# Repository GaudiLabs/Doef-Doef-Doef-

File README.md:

# Doef-Doef-Doef-
Groove Box Synthesiszer with SMD Sliders

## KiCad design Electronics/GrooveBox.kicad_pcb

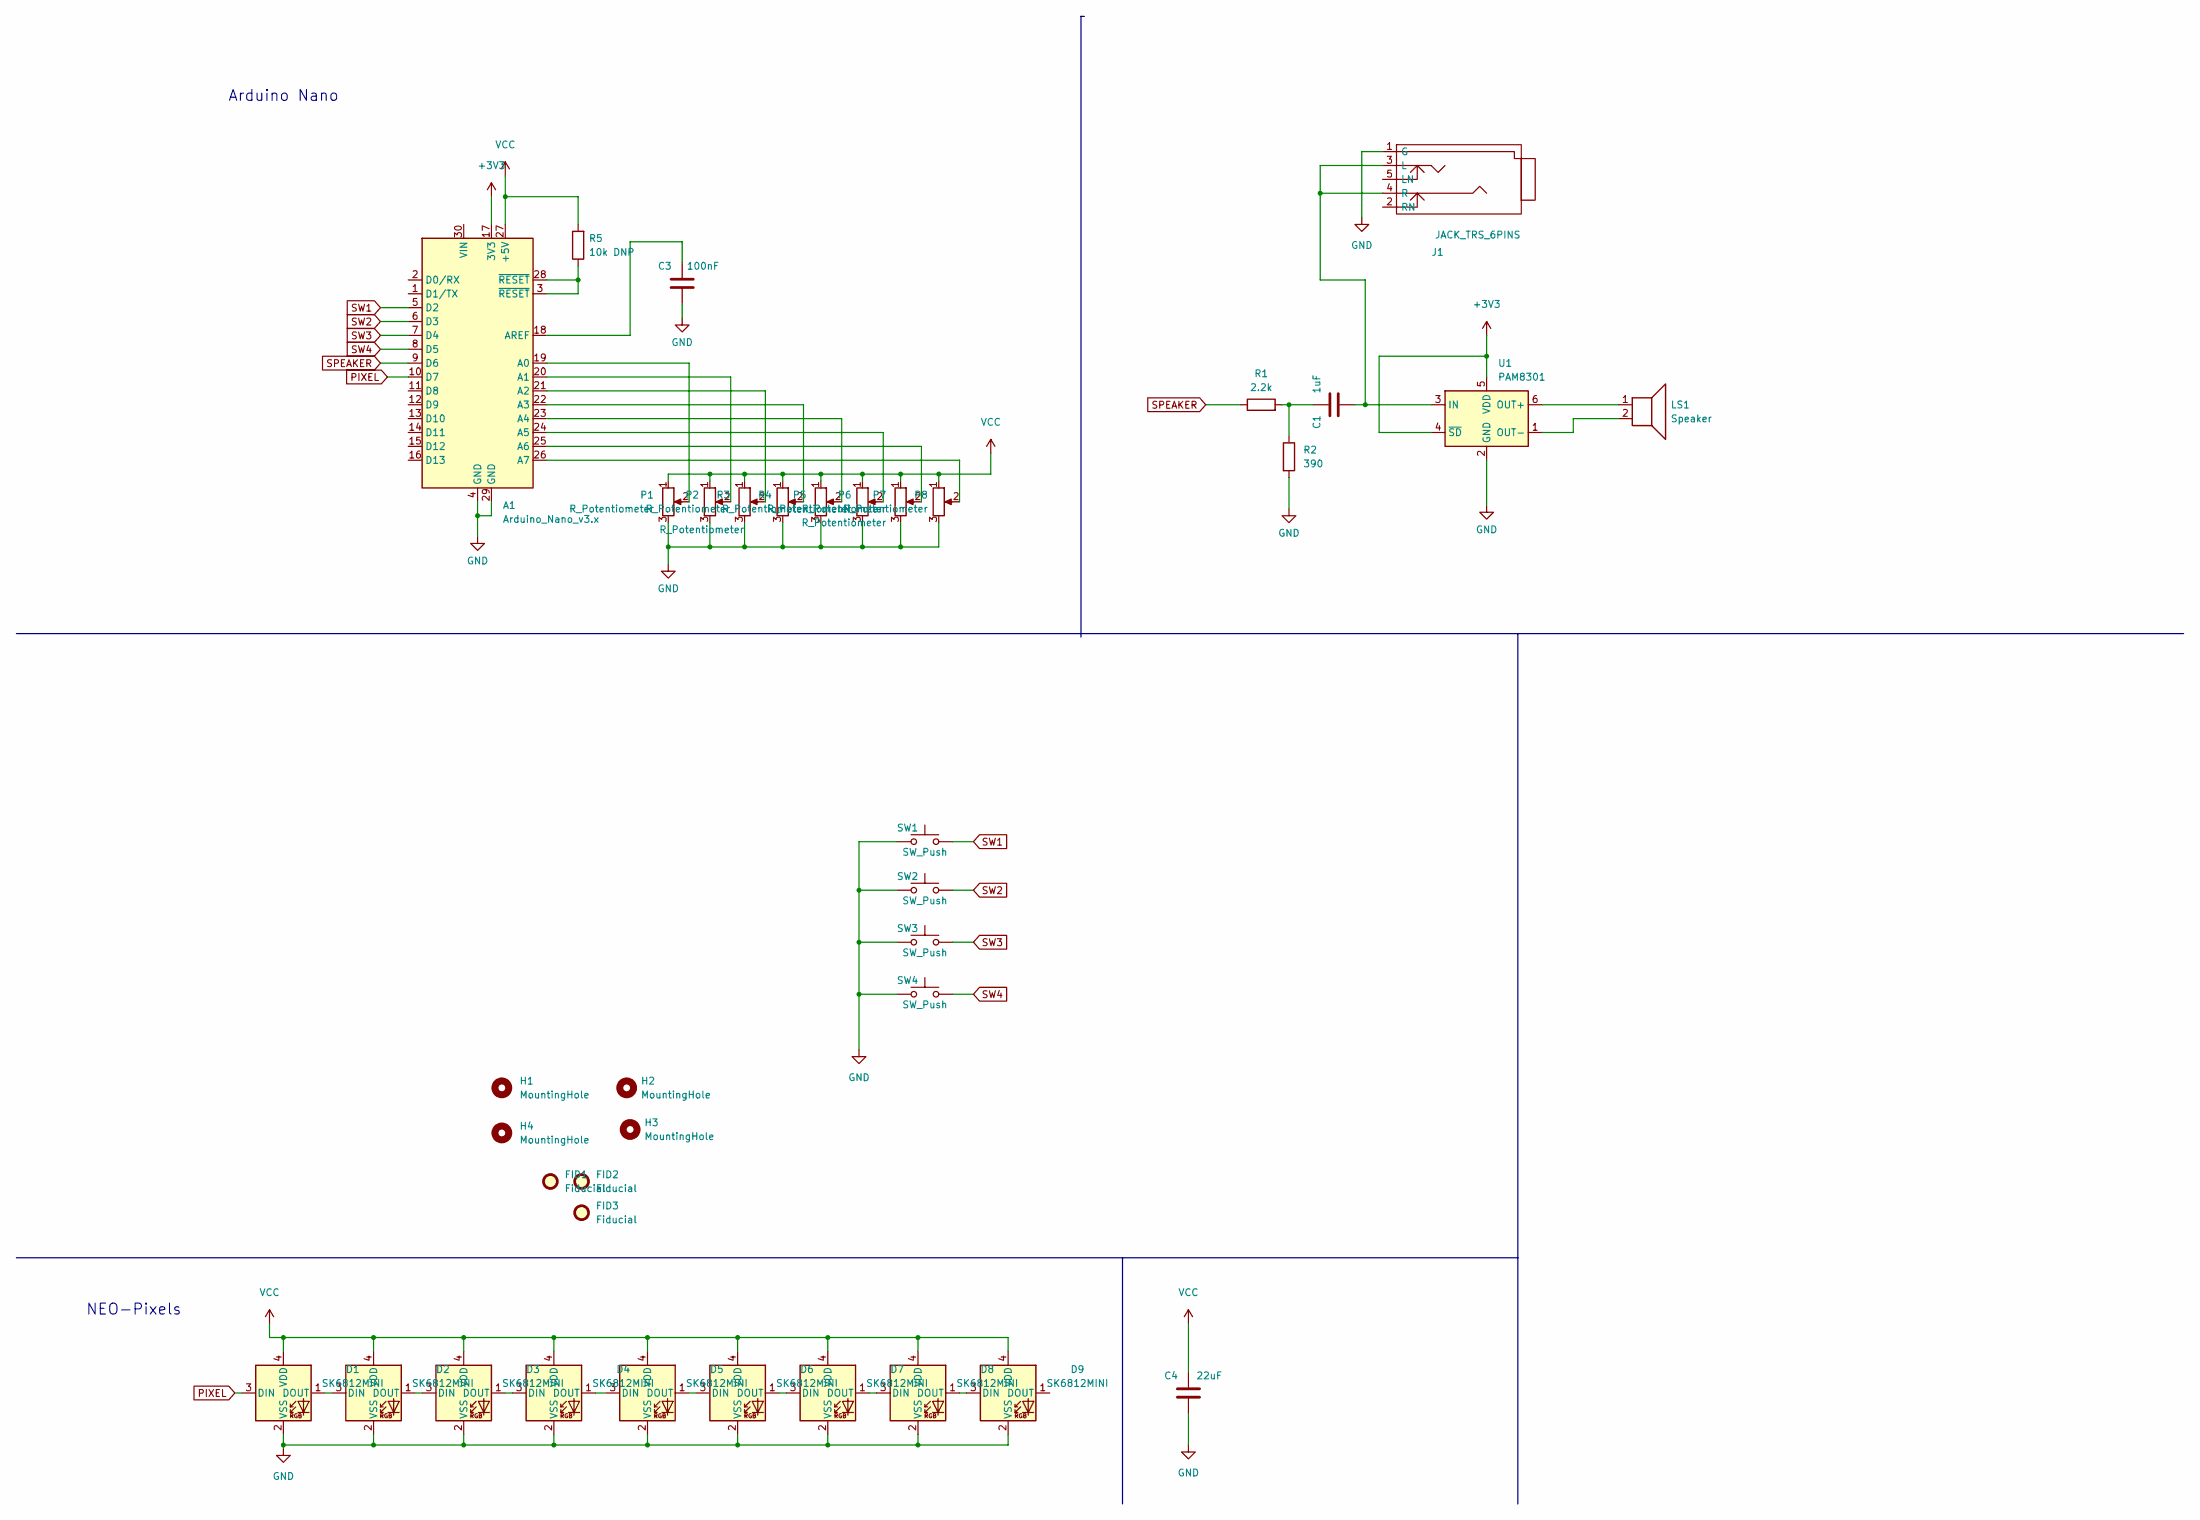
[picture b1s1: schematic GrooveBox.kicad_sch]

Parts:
A1: Arduino_Nano_v3.x; Arduino_Nano_SMD
C1: 1uF; C_0805_2012Metric
C3: 100nF; C_0805_2012Metric
C4: 22uF; C_0805_2012Metric
D1, D2, D3, D4, D5, D6, D7, D8, D9: SK6812MINI; LED_SK6812MINI_PLCC4_3.5x3.5mm_P1.75mm
FID1, FID2, FID3: Fiducial; Fiducial_1mm_Dia_2.54mm_Outer_CopperBottom
H1, H2, H3, H4: MountingHole; MountingHole_3.2mm_M3
J1: JACK_TRS_6PINS; Jack3_5_Switchcraft_35RASMT4BHNTRX
LS1: Speaker; Speaker16mm_circular
P1, P2, P5, P6, P7, P8: R_Potentiometer; TaidacentSlidingPot
R1: 2.2k; R_0805_2012Metric
R2: 390; R_0805_2012Metric
R3, R4: R_Potentiometer; TaidacentSlidingPot
R5: 10k DNP; R_0805_2012Metric
SW1, SW2, SW3, SW4: SW_Push; SW_SPST_TL3342
U1: PAM8301; SOT-23-6

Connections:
+3V3: A1.17 (3V3), U1.4 (~SD), U1.5 (VDD)
GND: A1.4 (GND), A1.29 (GND), C3.1, C4.1, D1.2 (VSS), D2.2 (VSS), D3.2 (VSS), D4.2 (VSS), D5.2 (VSS), D6.2 (VSS), D7.2 (VSS), D8.2 (VSS), D9.2 (VSS), J1.1 (G), P1.3, P2.3, P5.3, P6.3, P7.3, P8.3, R2.2, R3.3, R4.3, SW1.1, SW2.1, SW3.1, SW4.1, U1.2 (GND)
unnamed: A1.18 (AREF), C3.2
unnamed: A1.20 (A1), P2.2
unnamed: A1.21 (A2), R3.2
unnamed: A1.23 (A4), P5.2
unnamed: A1.26 (A7), P8.2
unnamed: A1.3 (~RESET), A1.28 (~RESET), R5.1
unnamed: C1.1, J1.3 (L), J1.4 (R), U1.3 (IN)
unnamed: C1.2, R1.2, R2.1
unnamed: D1.1 (DOUT), D2.3 (DIN)
unnamed: D2.1 (DOUT), D3.3 (DIN)
unnamed: D3.1 (DOUT), D4.3 (DIN)
unnamed: D4.1 (DOUT), D5.3 (DIN)
unnamed: D5.1 (DOUT), D6.3 (DIN)
unnamed: D6.1 (DOUT), D7.3 (DIN)
unnamed: D7.1 (DOUT), D8.3 (DIN)
unnamed: D8.1 (DOUT), D9.3 (DIN)
unnamed: LS1.1, U1.6 (OUT+)
unnamed: LS1.2, U1.1 (OUT-)
unnamed: A1.19 (A0), P1.2
unnamed: A1.24 (A5), P6.2
unnamed: A1.25 (A6), P7.2
unnamed: A1.22 (A3), R4.2
PIXEL: A1.10 (D7), D1.3 (DIN)
SPEAKER: A1.9 (D6), R1.1
SW1: A1.5 (D2), SW1.2
SW2: A1.6 (D3), SW2.2
SW3: A1.7 (D4), SW3.2
SW4: A1.8 (D5), SW4.2
VCC: A1.27 (+5V), C4.2, D1.4 (VDD), D2.4 (VDD), D3.4 (VDD), D4.4 (VDD), D5.4 (VDD), D6.4 (VDD), D7.4 (VDD), D8.4 (VDD), D9.4 (VDD), P1.1, P2.1, P5.1, P6.1, P7.1, P8.1, R3.1, R4.1, R5.2

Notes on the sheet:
Arduino Nano
NEO-Pixels

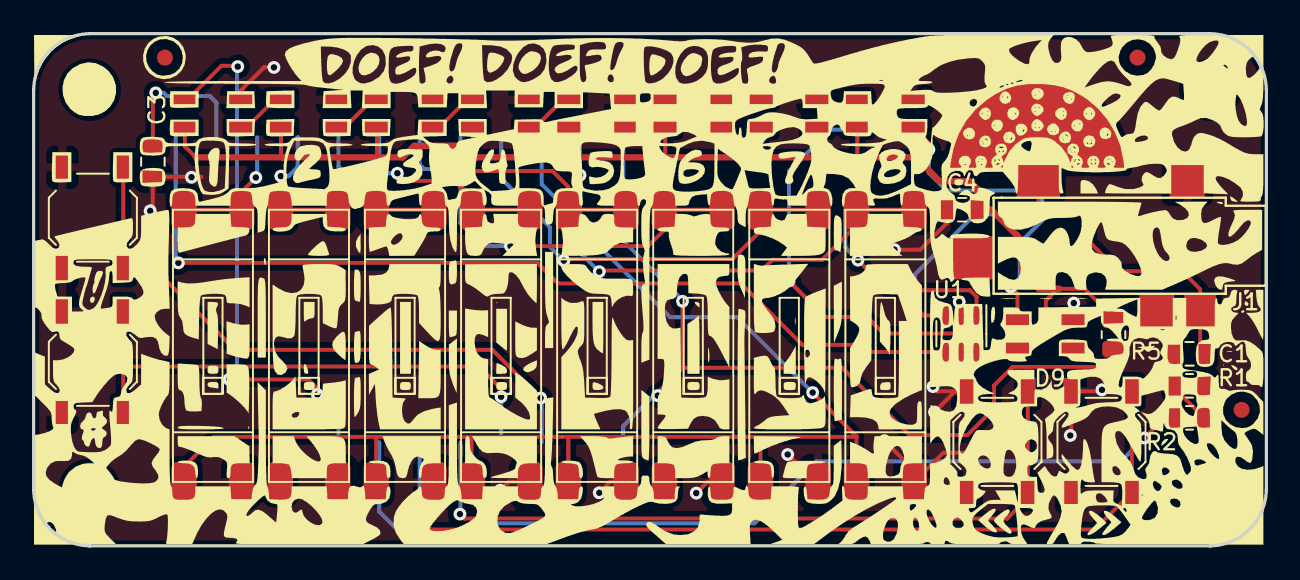
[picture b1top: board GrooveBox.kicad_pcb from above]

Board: 2 copper layers, 77.0 x 32.0 mm, 38 parts (1 on the bottom side), 31 nets.

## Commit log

2024-02-01 First Design Commit Yeah
2024-02-09 Version sent to PCB Manufacturing Yeah
